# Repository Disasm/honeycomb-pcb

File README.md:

# honeycomb

An experimental board with GW1NS-2C FPGA.

## Programming

To program the board you need [openFPGALoader](https://github.com/trabucayre/openFPGALoader).

SRAM programming:

```
openFPGALoader -b littleBee -c ft2232 bitstream.fs
```

Internal flash programming:

```
openFPGALoader -b littleBee -c ft2232 -f bitstream.fs
```

## JTAG interface firmware update

To update the firmware you need to reboot into a bootloader:
* Disconnect the board from USB and power supplies.
* Short 3.3V line and the first pin of the STM32F042 MCU.
* While shorting the pin, connect a USB cable.

Then update the firmware with dfu-util:

```
dfu-util -a 0 -s 0x08000000:leave -D firmware.bin
```

## Revision History

### 1.0: 2021-02-19

* First version.
* Errata:
    * 3.3V supply should be used for VCCX instead of 1.8V supply.
    * Power LED is too bright.
    * Resistor values on a schematic do not correspond to the available values.

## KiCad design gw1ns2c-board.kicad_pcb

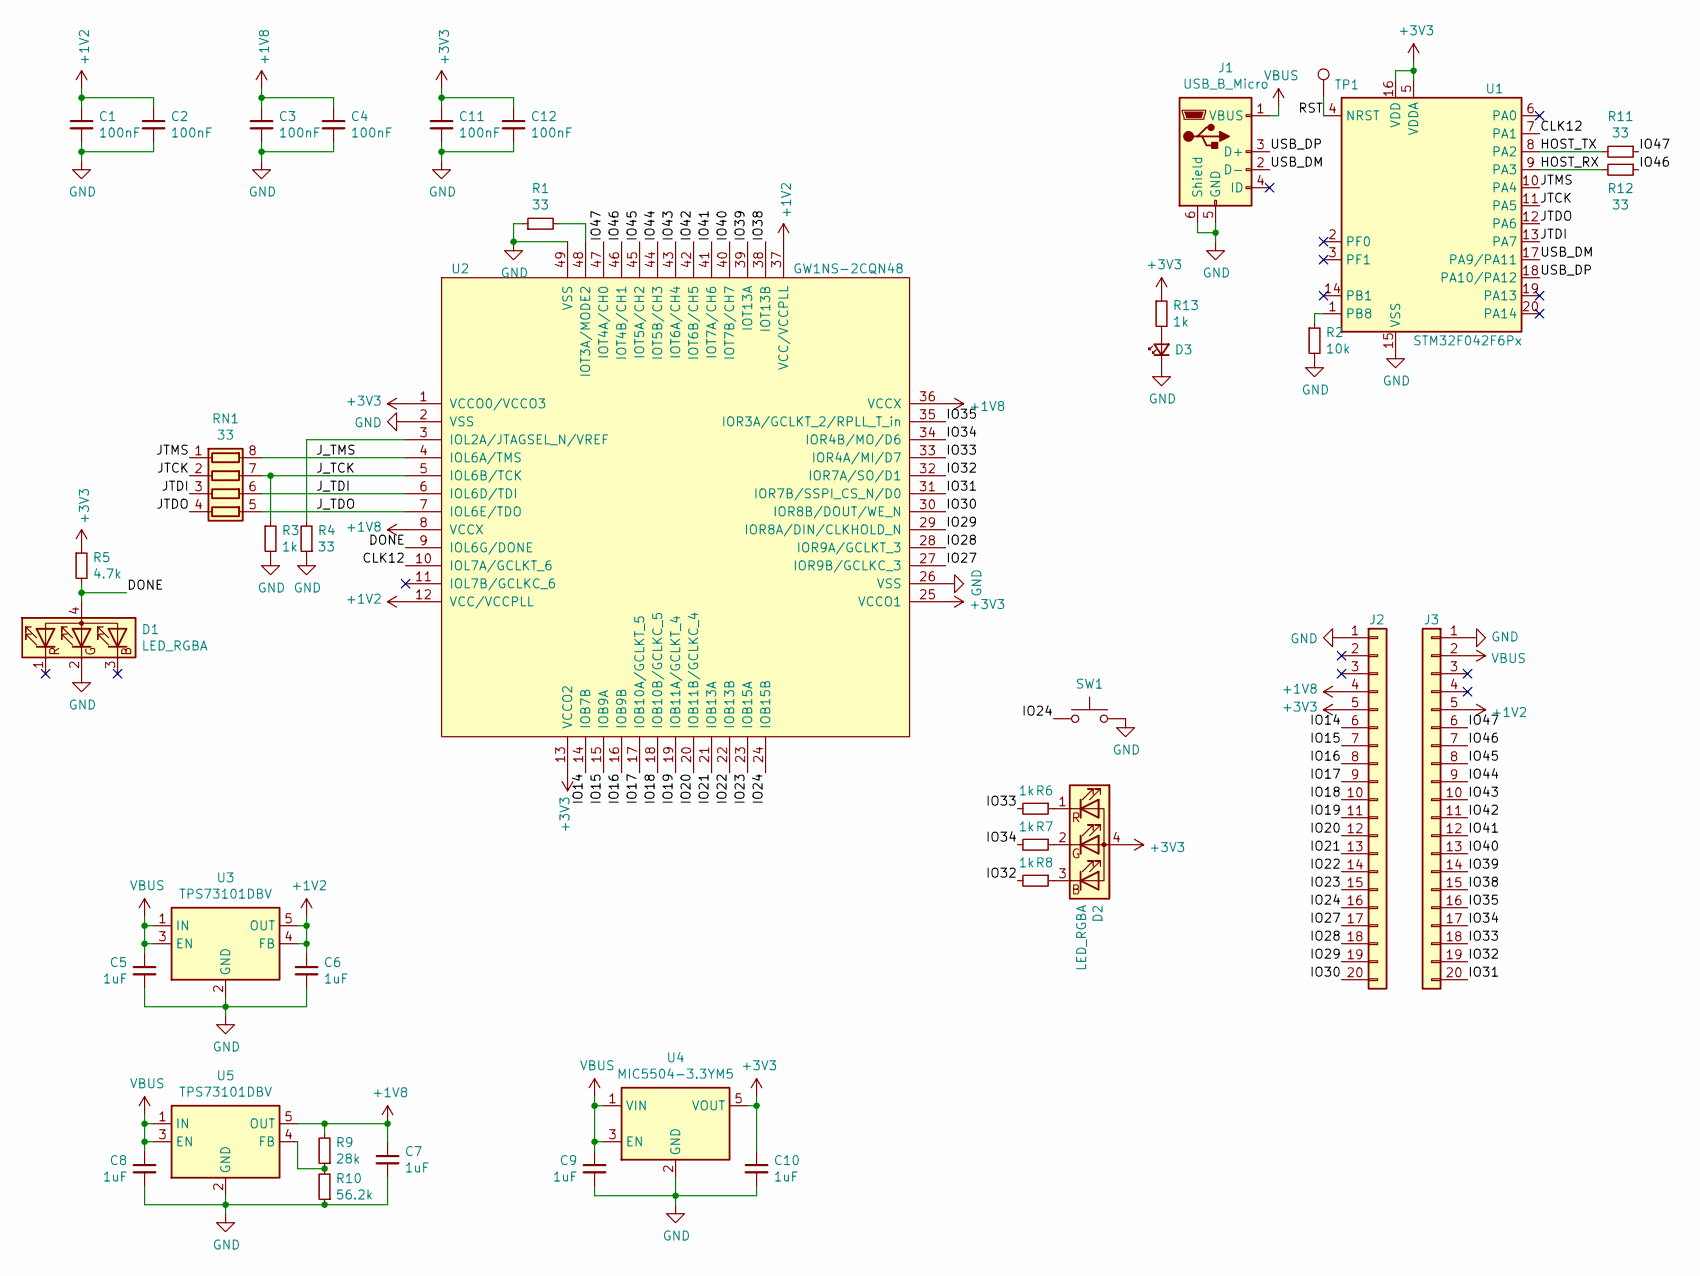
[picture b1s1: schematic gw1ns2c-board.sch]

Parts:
C1, C2, C3, C4, C11, C12: 100nF; C_0603_1608Metric
C5, C6, C7, C8, C9, C10: 1uF; C_0603_1608Metric
D1, D2: LED_RGBA; LED_LiteOn_LTST-C19HE1WT
D3: LED_Small; LED_1206_3216Metric
J1: USB_B_Micro; USB_Micro-B_Molex-105017-0001
J2, J3: Conn_01x20; PinHeader_1x20_P2.54mm_Vertical
R1, R4, R11, R12: 33; R_0603_1608Metric
R2: 10k; R_0603_1608Metric
R3, R6, R7, R8, R13: 1k; R_0603_1608Metric
R5: 4.7k; R_0603_1608Metric
R9: 28k; R_0603_1608Metric
R10: 56.2k; R_0603_1608Metric
RN1: 33; R_Array_Concave_4x0603
SW1: SW_Push; SW_SPST_B3U-1000P
TP1: TestPoint; TestPoint_Pad_D1.0mm
U1: STM32F042F6Px; TSSOP-20_4.4x6.5mm_P0.65mm
U2: GW1NS-2CQN48; QFN-48-1EP_6x6mm_P0.4mm_EP4.3x4.3mm
U3, U5: TPS73101DBV; SOT-23-5
U4: MIC5504-3.3YM5; SOT-23-5

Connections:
+1V2: C1.1, C2.1, C6.1, J3.5, U2.12 (VCC/VCCPLL), U2.37 (VCC/VCCPLL), U3.4 (FB), U3.5 (OUT)
+1V8: C3.1, C4.1, C7.1, J2.4, R9.2, U2.8 (VCCX), U2.36 (VCCX), U5.5 (OUT)
+3V3: C10.1, C11.1, C12.1, D2.4 (A), J2.5, R5.1, R13.1, U1.5 (VDDA), U1.16 (VDD), U2.1 (VCCO0/VCCO3), U2.13 (VCCO2), U2.25 (VCCO1), U4.5 (VOUT)
/CLK12: U1.7 (PA1), U2.10 (IOL7A/GCLKT_6)
/DONE: D1.4 (A), R5.2, U2.9 (IOL6G/DONE)
/HOST_RX: R12.2, U1.9 (PA3)
/HOST_TX: R11.2, U1.8 (PA2)
/IO14: J2.6, U2.14 (IOB7B)
/IO15: J2.7, U2.15 (IOB9A)
/IO16: J2.8, U2.16 (IOB9B)
/IO17: J2.9, U2.17 (IOB10A/GCLKT_5)
/IO18: J2.10, U2.18 (IOB10B/GCLKC_5)
/IO19: J2.11, U2.19 (IOB11A/GCLKT_4)
/IO20: J2.12, U2.20 (IOB11B/GCLKC_4)
/IO21: J2.13, U2.21 (IOB13A)
/IO22: J2.14, U2.22 (IOB13B)
/IO23: J2.15, U2.23 (IOB15A)
/IO24: J2.16, SW1.1, U2.24 (IOB15B)
/IO27: J2.17, U2.27 (IOR9B/GCLKC_3)
/IO28: J2.18, U2.28 (IOR9A/GCLKT_3)
/IO29: J2.19, U2.29 (IOR8A/DIN/CLKHOLD_N)
/IO30: J2.20, U2.30 (IOR8B/DOUT/WE_N)
/IO31: J3.20, U2.31 (IOR7B/SSPI_CS_N/D0)
/IO32: J3.19, R8.2, U2.32 (IOR7A/SO/D1)
/IO33: J3.18, R6.2, U2.33 (IOR4A/MI/D7)
/IO34: J3.17, R7.2, U2.34 (IOR4B/MO/D6)
/IO35: J3.16, U2.35 (IOR3A/GCLKT_2/RPLL_T_in)
/IO38: J3.15, U2.38 (IOT13B)
/IO39: J3.14, U2.39 (IOT13A)
/IO40: J3.13, U2.40 (IOT7B/CH7)
/IO41: J3.12, U2.41 (IOT7A/CH6)
/IO42: J3.11, U2.42 (IOT6B/CH5)
/IO43: J3.10, U2.43 (IOT6A/CH4)
/IO44: J3.9, U2.44 (IOT5B/CH3)
/IO45: J3.8, U2.45 (IOT5A/CH2)
/IO46: J3.7, R12.1, U2.46 (IOT4B/CH1)
/IO47: J3.6, R11.1, U2.47 (IOT4A/CH0)
/JTCK: RN1.2 (R2.1), U1.11 (PA5)
/JTDI: RN1.3 (R3.1), U1.13 (PA7)
/JTDO: RN1.4 (R4.1), U1.12 (PA6)
/JTMS: RN1.1 (R1.1), U1.10 (PA4)
/J_TCK: R3.1, RN1.7 (R2.2), U2.5 (IOL6B/TCK)
/J_TDI: RN1.6 (R3.2), U2.6 (IOL6D/TDI)
/J_TDO: RN1.5 (R4.2), U2.7 (IOL6E/TDO)
/J_TMS: RN1.8 (R1.2), U2.4 (IOL6A/TMS)
/RST: TP1.1, U1.4 (NRST)
/USB_DM: J1.2 (D-), U1.17 (PA9/PA11)
/USB_DP: J1.3 (D+), U1.18 (PA10/PA12)
GND: C1.2, C2.2, C3.2, C4.2, C5.2, C6.2, C7.2, C8.2, C9.2, C10.2, C11.2, C12.2, D1.2 (GK), D3.1 (K), J1.5 (GND), J1.6 (Shield), J2.1, J3.1, R1.1, R2.2, R3.2, R4.1, R10.1, SW1.2, U1.15 (VSS), U2.2 (VSS), U2.26 (VSS), U2.49 (VSS), U3.2 (GND), U4.2 (GND), U5.2 (GND)
unnamed: D2.1 (RK), R6.1
unnamed: D2.2 (GK), R7.1
unnamed: D2.3 (BK), R8.1
unnamed: D3.2 (A), R13.2
unnamed: R1.2, U2.48 (IOT3A/MODE2)
unnamed: R2.1, U1.1 (PB8)
unnamed: R4.2, U2.3 (IOL2A/JTAGSEL_N/VREF)
unnamed: R9.1, R10.2, U5.4 (FB)
VBUS: C5.1, C8.1, C9.1, J1.1 (VBUS), J3.2, U3.1 (IN), U3.3 (EN), U4.1 (VIN), U4.3 (EN), U5.1 (IN), U5.3 (EN)

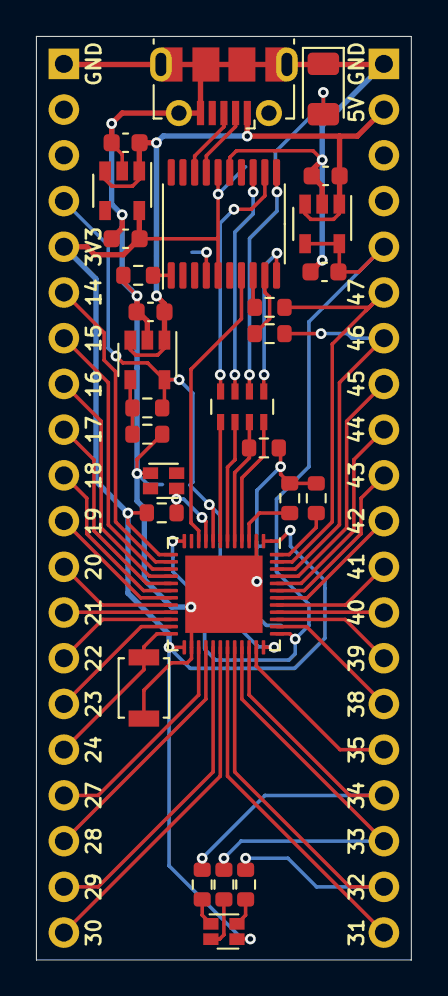
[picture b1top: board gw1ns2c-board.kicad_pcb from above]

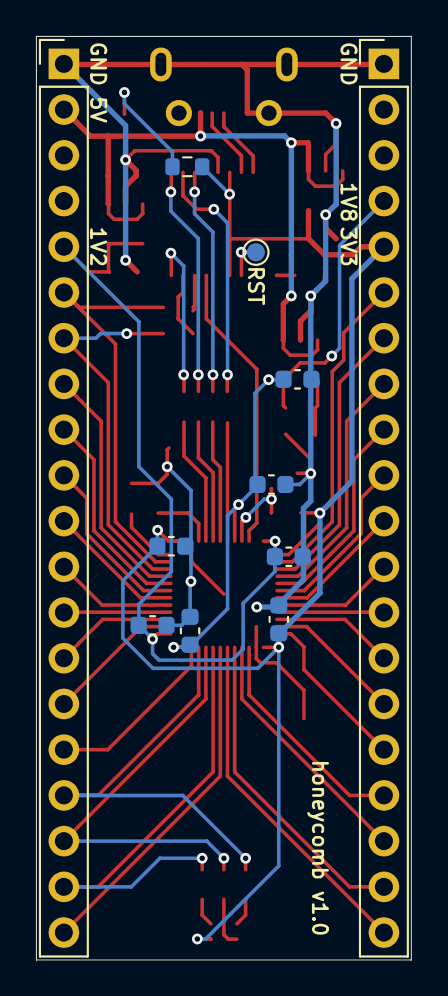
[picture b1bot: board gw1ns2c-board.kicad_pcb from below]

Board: 2 copper layers, 20.8 x 51.3 mm, 39 parts (11 on the bottom side), 58 nets.

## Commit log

2021-02-19 Add .gitignore
2021-02-19 Add GW1NS-2C library
2021-02-19 Add board schematics and layout
2021-02-19 Add gerbers
2021-02-19 Generate Interactive BOM
2021-02-19 Generate schematic PDF
2021-02-19 Add post-assembly notes
2021-02-23 Add README.md
2021-02-23 Add programming and fw update sections
2021-02-23 Add PCB render
